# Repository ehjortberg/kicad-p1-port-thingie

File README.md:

# P1 Port Thingie
This is a small board to bridge the P1 port of the Swedish electricity meters with Home Assistant.
The level conversion part of the schematics is based on the examples on the [software](https://github.com/psvanstrom/esphome-p1reader) github page.
The rest is basically a 5v to 3.3V LDO and ESP07 required components.

It can be programmed with esphome using a 3.3V ftdi cable or similar. External power via rj12 is probably needed as the ftdi cables usually do not have enough power on 3.3V
Installation guide and software: [https://github.com/psvanstrom/esphome-p1reader](https://github.com/psvanstrom/esphome-p1reader).

Edit the p1reader.yaml and set board: esp01_1m

There is sometimes interference on the RX line when programming so it's preferable to program before adding the transistor.

A box can be 3D Printed. [Download .stl files](https://www.thingiverse.com/thing:5337456)

# BOM

| Reference | Value | Footprint |
| --------- | ----- | --------- |
|Button1||Button_Switch_SMD:SW_SPST_TL3342|
|Button2||Button_Switch_SMD:SW_SPST_TL3342|
|C1|100nF|Capacitor_Tantalum_SMD:CP_EIA-6032-15_Kemet-U_Pad2.25x2.35mm_HandSolder|
|C2|100nF|Capacitor_Tantalum_SMD:CP_EIA-6032-15_Kemet-U_Pad2.25x2.35mm_HandSolder|
|JP1 Connector|6P6C|Connector_RJ:RJ12_Amphenol_54601|
|Q1|BC817W.115|Package_TO_SOT_SMD:SOT-323_SC-70|
|R1|4K7|Resistor_SMD:R_0805_2012Metric_Pad1.20x1.40mm_HandSolder|
|R2,R3,R4,R5,R6,R7|10K|Resistor_SMD:R_0805_2012Metric_Pad1.20x1.40mm_HandSolder|
|U1|LD1117S33CTR|Package_TO_SOT_SMD:SOT-223-3_TabPin2|
|ESP07|||

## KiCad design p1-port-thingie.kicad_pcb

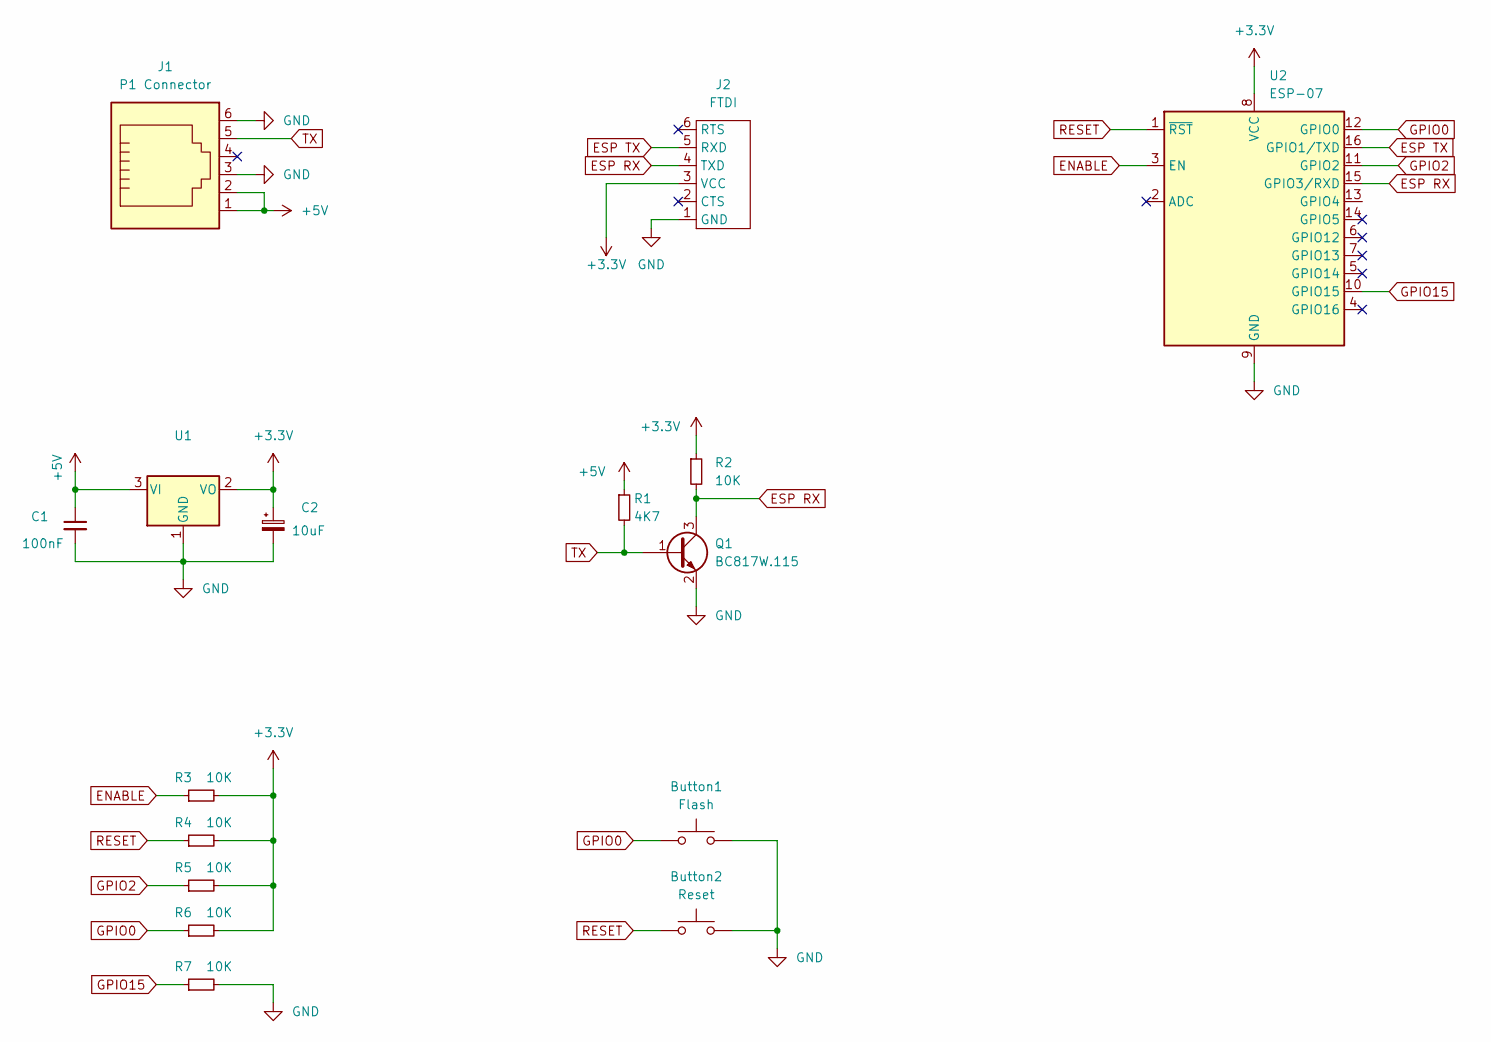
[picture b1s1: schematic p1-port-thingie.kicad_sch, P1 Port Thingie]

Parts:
Button1: Flash; SW_SPST_TL3342
Button2: Reset; SW_SPST_TL3342
C1: 100nF; CP_EIA-6032-15_Kemet-U_Pad2.25x2.35mm_HandSolder
C2: 10uF; CP_EIA-6032-15_Kemet-U_Pad2.25x2.35mm_HandSolder
J1: P1 Connector; RJ12_Amphenol_54601
J2: FTDI
Q1: BC817W.115; SOT-323_SC-70
R1: 4K7; R_0805_2012Metric_Pad1.20x1.40mm_HandSolder
R2, R3, R4, R5, R6, R7: 10K; R_0805_2012Metric_Pad1.20x1.40mm_HandSolder
U1: (no value)
U2: ESP-07

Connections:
+3V3: C2.1, J2.3 (VCC), R2.1, R3.2, R4.2, R5.2, R6.2, U1.2 (VO), U2.8 (VCC)
+5V: C1.1, J1.1, J1.2, R1.1, U1.3 (VI)
ENABLE: R3.1, U2.3 (EN)
ESP RX: J2.4 (TXD), Q1.3 (C), R2.2, U2.15 (GPIO3/RXD)
ESP TX: J2.5 (RXD), U2.16 (GPIO1/TXD)
GND: Button1.2, Button2.2, C1.2, C2.2, J1.3, J1.6, J2.1 (GND), Q1.2 (E), R7.2, U1.1 (GND), U2.9 (GND)
GPIO0: Button1.1, R6.1, U2.12 (GPIO0)
GPIO2: R5.1, U2.11 (GPIO2)
GPIO15: R7.1, U2.10 (GPIO15)
RESET: Button2.1, R4.1, U2.1 (~RST)
TX: J1.5, Q1.1 (B), R1.2

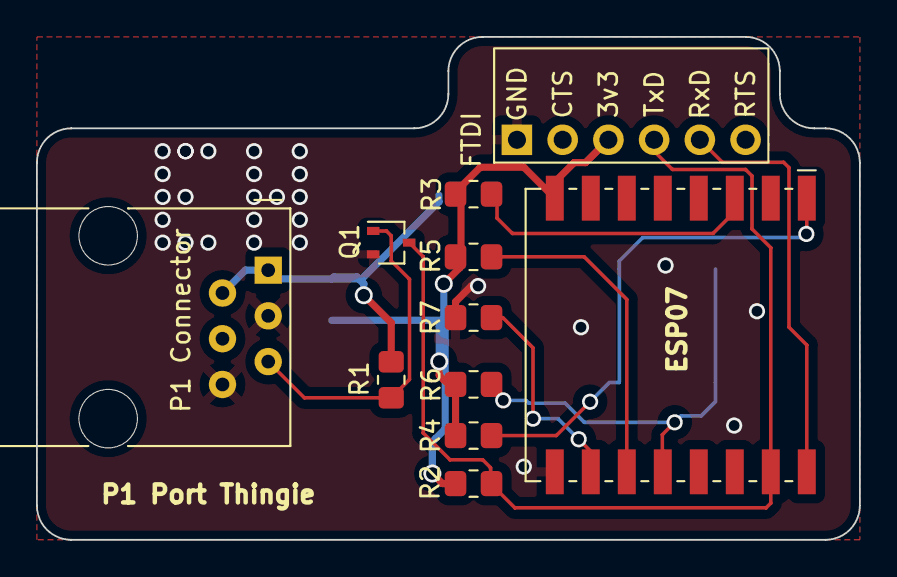
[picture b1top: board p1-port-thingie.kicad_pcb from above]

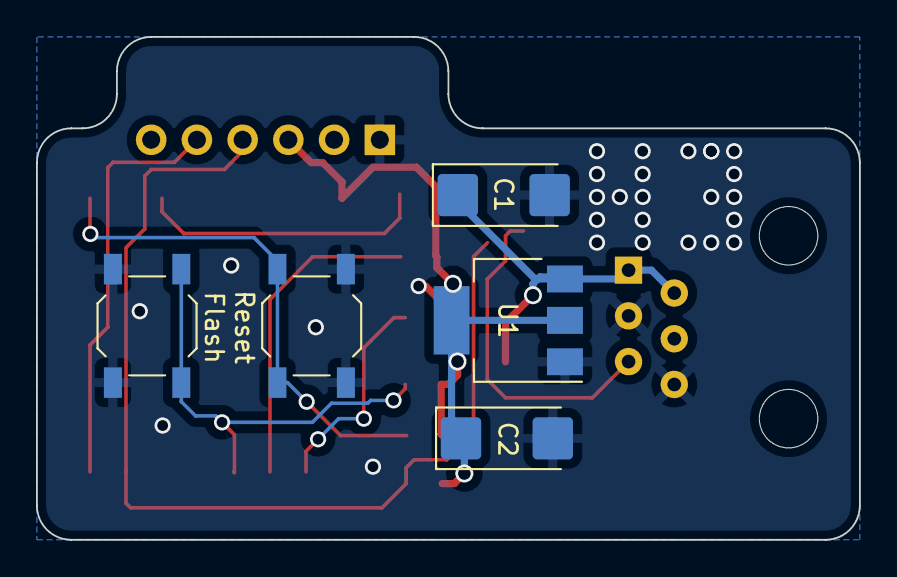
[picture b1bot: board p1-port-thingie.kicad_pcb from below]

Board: 2 copper layers, 45.7 x 27.9 mm, 16 parts (5 on the bottom side), 11 nets.

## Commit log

2022-04-01 Take 2
2022-04-01 Link to .stl files on Thingiverse
